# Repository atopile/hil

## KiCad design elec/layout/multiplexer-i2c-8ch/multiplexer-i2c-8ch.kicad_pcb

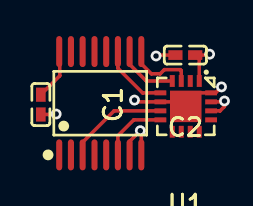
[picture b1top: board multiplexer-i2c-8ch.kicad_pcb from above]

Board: 2 copper layers, 4 parts (0 on the bottom side), 7 nets.

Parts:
C1: 100nF ±10% 16V X7R; C0402-b3ef17
C2: 1µF ±10% 25V X5R; C0402-b3ef17
U1: QFN-16_L3.0-W3.0-P0.50-BL-EP1.7-3a4c56
U2: TSSOP-16_L5.0-W4.4-P0.65-LS6.4-BL-4f6acc

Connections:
A: U1.7, U2.3
Eh: U1.8, U2.6
S0: U1.5, U2.11
S1: U1.4, U2.10
S2: U1.3, U2.9
gnd: C1.2, C2.2, U1.6, U1.17, U2.7, U2.8
hv: C1.1, C2.1, U1.1, U1.14, U1.15, U1.16, U2.16

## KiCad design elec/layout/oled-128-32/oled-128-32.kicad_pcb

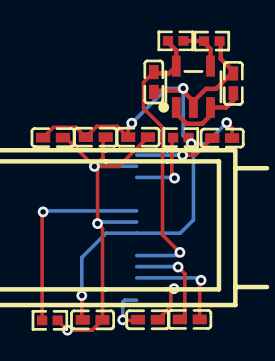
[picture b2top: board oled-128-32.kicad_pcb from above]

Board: 2 copper layers, 15 parts (0 on the bottom side), 11 nets.

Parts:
C1, C2, C3, C4: 1µF ±10% 25V X5R; C0402-b3ef17
C5, C7, C8, C9: 100nF ±10% 16V X7R; C0402-b3ef17
C6: 4.7µF ±10% 10V X5R; C0402-b3ef17
OLED1: OLED-SMD_N087-2832TSWYG02-H14_1-7d3a70
R1: 510kΩ ±1% 62.5mW; R0402-56259e
R2, R4: 10kΩ ±1% 62.5mW; R0402-56259e
R3: 25.5kΩ ±1% 62.5mW; R0402-56259e
U1: SOT-23-5_L3.0-W1.7-P0.95-LS2.8-BL

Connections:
ADJ_NC: R2.1, R3.2, U1.4
C1N: C1.1, OLED1.4
C1P: C1.2, OLED1.3
C2N: C2.1, OLED1.2
C2P: C2.2, OLED1.1
IREF: OLED1.12, R1.1
RESh: OLED1.9, R4.1
gnd: C3.2, C4.2, C5.2, C6.2, C7.2, C8.2, C9.2, OLED1.7, R1.2, R2.2, U1.2
hv: C5.1, C6.1, C7.1, C8.1, C9.1, OLED1.8, OLED1.13, OLED1.14, R4.2
hv-1: C3.1, U1.1, U1.3
hv-2: C4.1, OLED1.5, R3.1, U1.5

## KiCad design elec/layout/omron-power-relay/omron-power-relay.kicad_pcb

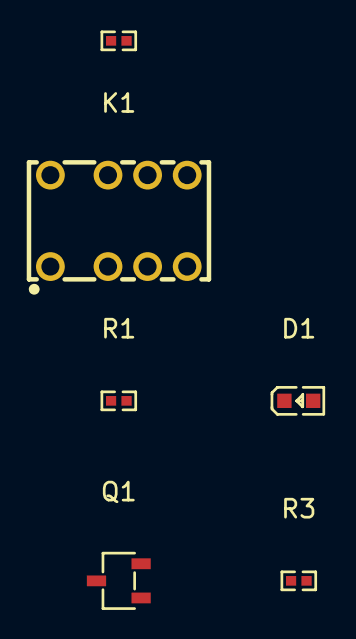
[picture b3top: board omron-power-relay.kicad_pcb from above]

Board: 2 copper layers, 6 parts (0 on the bottom side), 6 nets, no tracks yet.

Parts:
D1: LED0603-RD-c81ffb
K1: RELAY-TH_HFDXXX-689a1e
Q1: SOT-23-3_L2.9-W1.6-P1.90-LS2.8-BR-186170
R1: 10kΩ ±1% 62.5mW; R0402-56259e
R2, R3: 1kΩ ±1% 62.5mW; R0402-56259e

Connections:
cathode: D1.1, R3.1
gate: Q1.1, R1.2
gnd-1: Q1.2, R2.2
gnd-2: K1.8, Q1.3, R3.2
hv-1: D1.2, K1.1
line: R1.1, R2.1

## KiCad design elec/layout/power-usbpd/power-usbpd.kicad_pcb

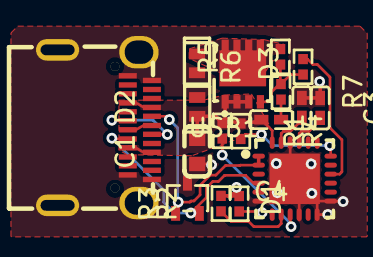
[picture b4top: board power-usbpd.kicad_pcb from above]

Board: 2 copper layers, 17 parts (0 on the bottom side), 17 nets.

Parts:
C1: 4.7µF ±10% 35V X5R; C0603-bd72f6
C2, C3: 1µF ±10% 25V X5R; C0402-b3ef17
C4: 100nF ±10% 16V X7R; C0402-b3ef17
D1: SOT-323-3_L2.1-W1.3-P1.32-LS2.1-BR-ee9edb
D2, D3: DFN1610-2_L1.6-W1.0-P1.05-RD-57a24e
Q1: PDFN3333-8_L3.1-W3.2-P0.65-LS3.4-BL-33e04e
R1, R4: 1kΩ ±1% 62.5mW; R0402-56259e
R2, R3: 4.7kΩ ±1% 62.5mW; R0402-56259e
R5: 100kΩ ±1% 62.5mW; R0402-56259e
R6: 22kΩ ±1% 62.5mW; R0402-56259e
R7: 100Ω ±1% 62.5mW; R0402-56259e
U1: QFN-24_L4.0-W4.0-P0.50-BL-EP2.8-2a85a7
USB1: USB-C-SMD_TYC-324G-a50b79

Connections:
A6: USB1.A6, USB1.B6
A7: USB1.A7, USB1.B7
DISCH: R1.2, U1.9
VBUS: C1.2, C4.2, D2.1, Q1.1, Q1.2, Q1.3, R1.1, R4.1, U1.24, USB1.A4, USB1.A9, USB1.B4, USB1.B9
VBUS_EN_SNK: R6.2, U1.16
VBUS_VS_DISCH: R4.2, U1.18
drain: D3.1, Q1.5, Q1.6, Q1.7, Q1.8, Q1.9, R5.2
gate: Q1.4, R5.1, R6.1, R7.1
gnd: C1.1, C2.1, C3.1, D1.3, D2.2, D3.2, U1.6, U1.10, U1.12, U1.13, U1.22, U1.25, USB1.1, USB1.2, USB1.3, USB1.4, USB1.A1, USB1.A12, USB1.B1, USB1.B12
hv: R2.2, R3.2
line: R3.1, U1.8
line-1: D1.1, U1.1, U1.2, USB1.A5
line-2: R2.1, U1.7
line-3: D1.2, U1.4, U1.5, USB1.B5
pd_controller-hv: C2.2, U1.21
pd_controller-hv-1: C3.2, U1.23
pd_controller-net: C4.1, R7.2

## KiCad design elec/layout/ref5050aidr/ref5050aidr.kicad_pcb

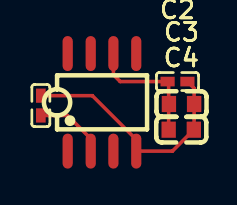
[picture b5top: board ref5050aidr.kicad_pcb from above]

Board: 2 copper layers, 5 parts (0 on the bottom side), 3 nets.

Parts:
C1, C2: 1µF ±10% 25V X5R; C0402-b3ef17
C3, C4: 10µF ±10% 10V X5R; C0603-bd72f6
U1: SOIC-8_L5.0-W4.0-P1.27-LS6.0-BL-294f77

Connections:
VIN: C1.1, U1.2
gnd: C1.2, C2.2, C3.2, C4.2, U1.4
hv: C2.1, C3.1, C4.1, U1.6

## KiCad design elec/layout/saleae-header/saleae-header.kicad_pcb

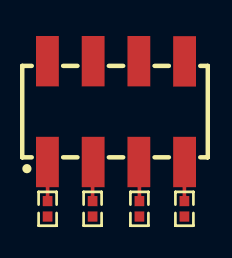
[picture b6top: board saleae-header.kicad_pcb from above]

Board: 2 copper layers, 5 parts (0 on the bottom side), 5 nets.

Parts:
R1, R2, R3, R4: 1kΩ ±1% 62.5mW; R0402-56259e
U1: HDR-SMD_8P-P2.54-V-M-R2-C4-LS7.4

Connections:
gnd: U1.2, U1.4, U1.6, U1.8
net: R3.2, U1.5
net-1: R4.2, U1.7
net-2: R2.2, U1.3
net-3: R1.2, U1.1
